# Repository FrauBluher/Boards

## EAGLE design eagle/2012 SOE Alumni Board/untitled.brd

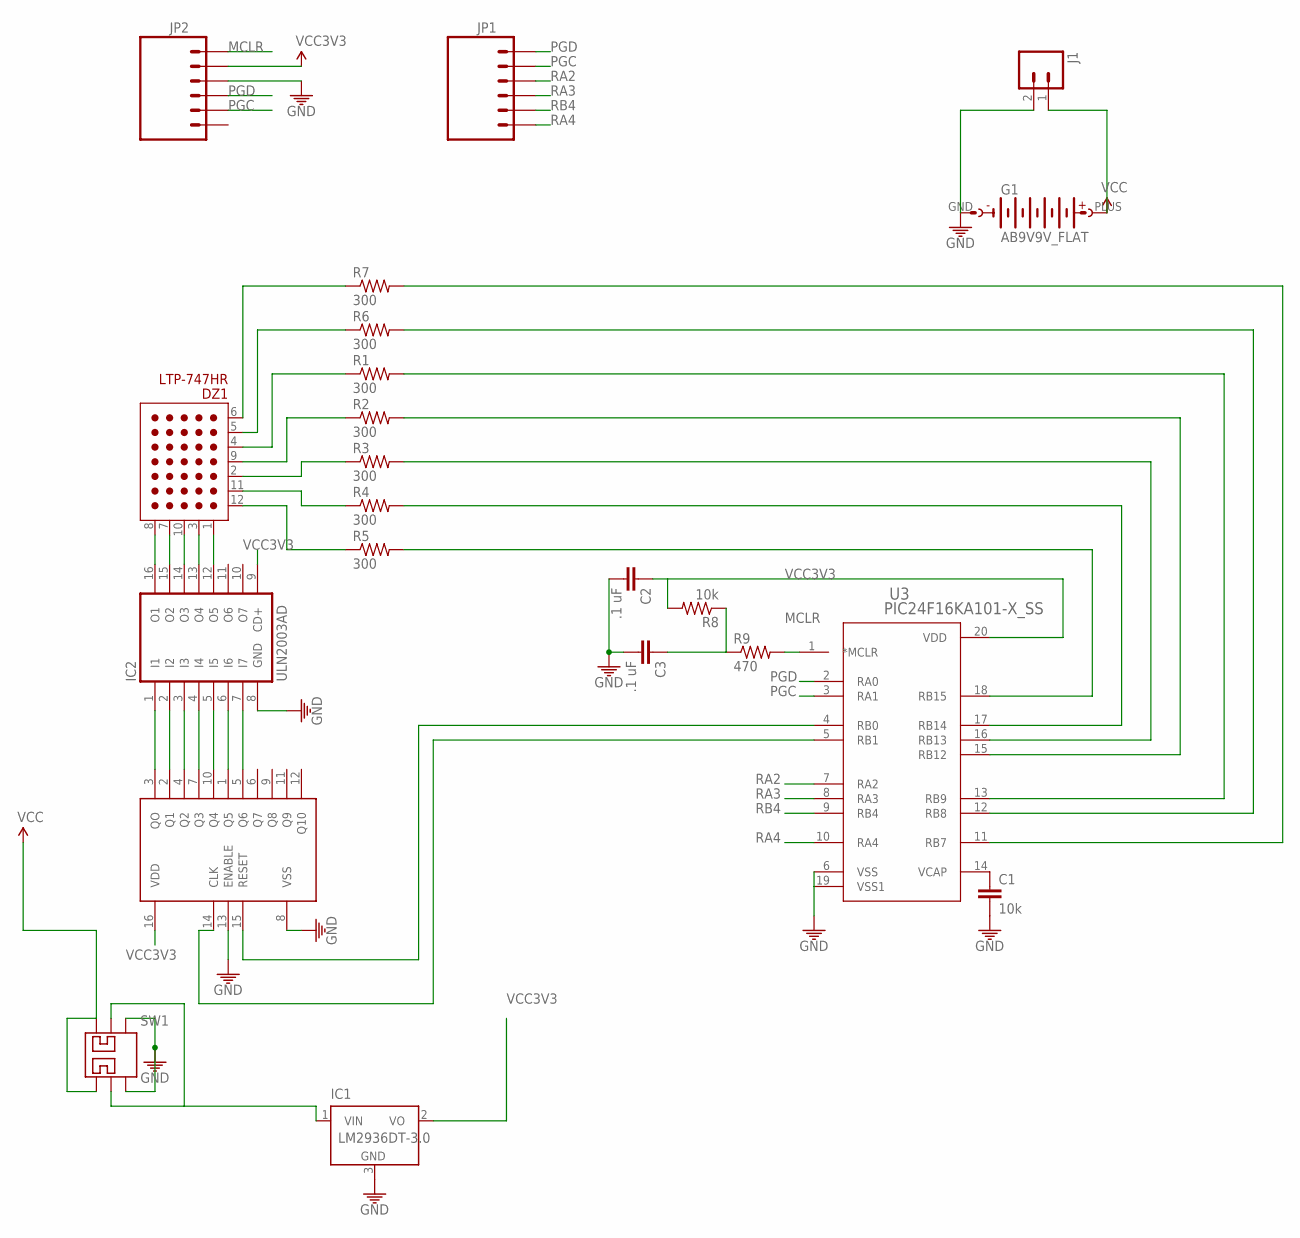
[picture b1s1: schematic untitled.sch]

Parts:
C1: 10k; 1206
C2, C3: .1 uF; 1206
DZ1: LTP-747HR
G1: AB9V9V_FLAT; BH9VPC
IC1: LM2936DT-3.0; TO252
IC2: ULN2003AD; SO16
J1: M02PTH; 1X02
JP1, JP2: M06LOCK; 1X06_LOCK
R1, R2, R3, R4, R5, R6, R7: 300; 0805
R8: 10k; 0805
R9: 470; 0805
SW1: SLIDE_SWITCH_DPDTTOP; EG2207
U1: MC14017B; SO16
U3: PIC24F16KA101-X_SS; SSOP20_MC

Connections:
GND: C1.2, C2.2, C3.2, G1.GND (-), IC1.3 (GND), IC2.8 (GND), J1.2 (1), JP2.3, SW1.P$3, SW1.P$6, U1.8 (VSS), U1.13 (ENABLE), U3.6 (VSS), U3.19 (VSS1)
MCLR: JP2.1, R9.2, U3.1 (*MCLR)
unnamed: DZ1.8 (C5), IC2.16 (O1)
unnamed: DZ1.7 (C4), IC2.15 (O2)
unnamed: DZ1.10 (C3), IC2.14 (O3)
unnamed: DZ1.3 (C2), IC2.13 (O4)
unnamed: DZ1.1 (C1), IC2.12 (O5)
unnamed: IC2.1 (I1), U1.3 (QO)
unnamed: IC2.2 (I2), U1.2 (Q1)
unnamed: IC2.3 (I3), U1.4 (Q2)
unnamed: IC2.4 (I4), U1.7 (Q3)
unnamed: IC2.5 (I5), U1.10 (Q4)
unnamed: IC2.6 (I6), U1.1 (Q5)
unnamed: IC2.7 (I7), U1.5 (Q6)
unnamed: U1.15 (RESET), U3.4 (RB0)
unnamed: U1.14 (CLK), U3.5 (RB1)
unnamed: DZ1.6 (R7), R7.1
unnamed: C1.1, U3.14 (VCAP)
unnamed: DZ1.5 (R6), R6.1
unnamed: DZ1.4 (R5), R1.1
unnamed: DZ1.9 (R4), R2.1
unnamed: DZ1.2 (R3), R3.1
unnamed: DZ1.11 (R2), R4.1
unnamed: DZ1.12 (R1), R5.1
unnamed: IC1.1 (VIN), SW1.P$2, SW1.P$5
unnamed: R5.2, U3.18 (RB15)
unnamed: R4.2, U3.17 (RB14)
unnamed: R3.2, U3.16 (RB13)
unnamed: R2.2, U3.15 (RB12)
unnamed: R1.2, U3.13 (RB9)
unnamed: R6.2, U3.12 (RB8)
unnamed: R7.2, U3.11 (RB7)
unnamed: C3.1, R8.1, R9.1
PGC: JP1.2, JP2.5, U3.3 (RA1)
PGD: JP1.1, JP2.4, U3.2 (RA0)
RA2: JP1.3, U3.7 (RA2)
RA3: JP1.4, U3.8 (RA3)
RA4: JP1.6, U3.10 (RA4)
RB4: JP1.5, U3.9 (RB4)
VCC: G1.PLUS (+), J1.1 (2), SW1.P$1, SW1.P$4
VCC3V3: C2.1, IC1.2 (VO), IC2.9 (CD+), JP2.2, R8.2, U1.16 (VDD), U3.20 (VDD)

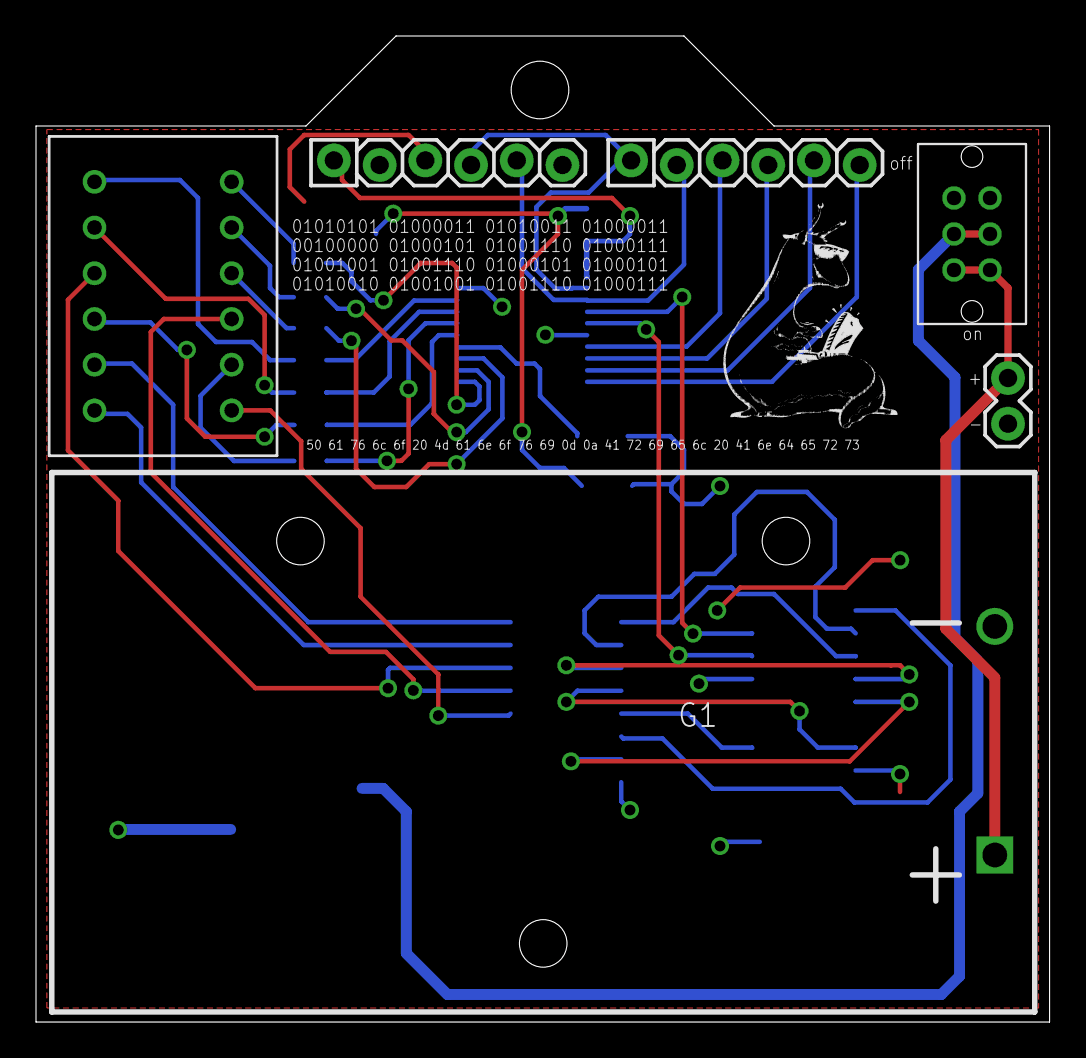
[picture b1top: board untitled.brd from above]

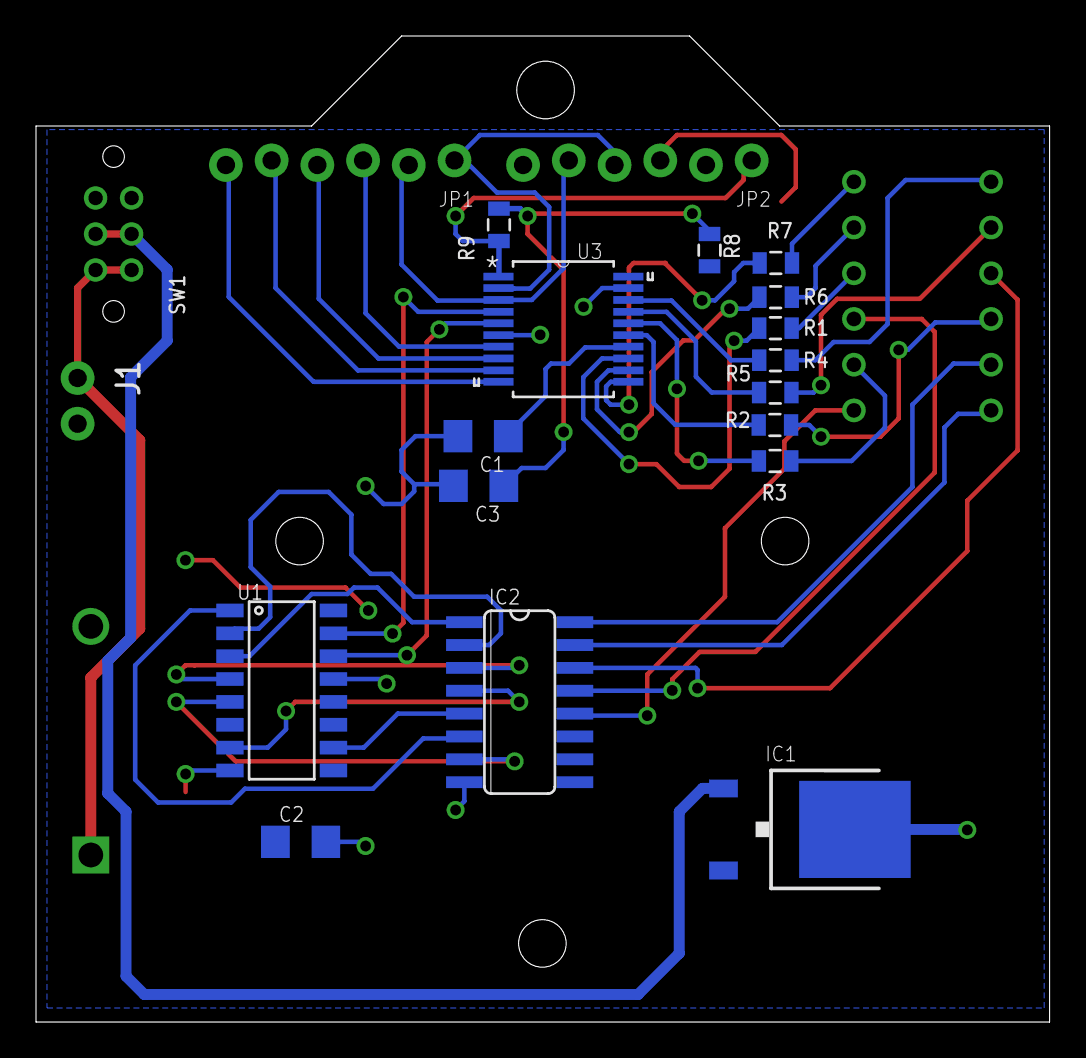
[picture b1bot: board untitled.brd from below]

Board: 2 copper layers, 56.3 x 54.8 mm, 22 parts (16 on the bottom side), 41 nets.

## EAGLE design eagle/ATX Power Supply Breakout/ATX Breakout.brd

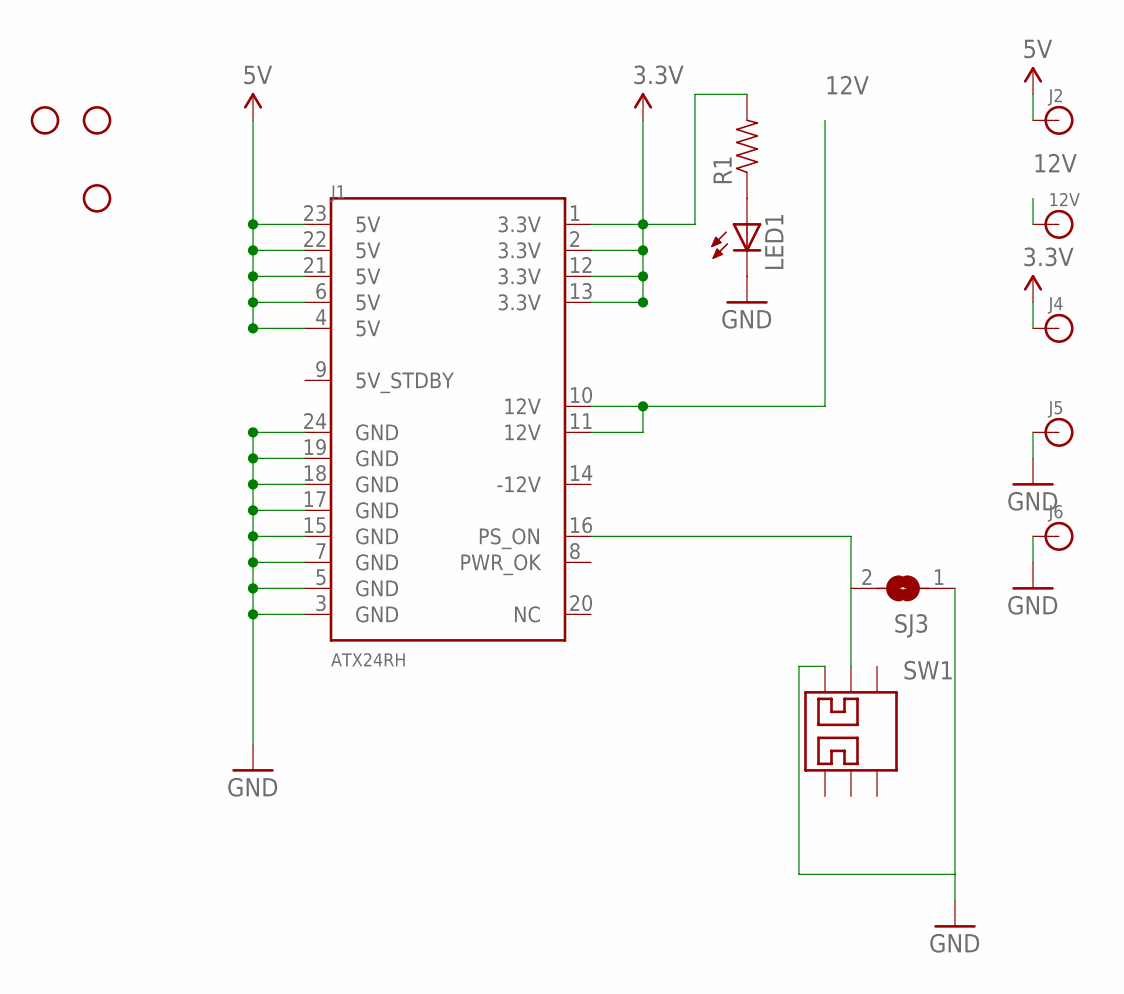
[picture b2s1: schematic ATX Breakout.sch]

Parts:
12V: BANANA_CONN
J1: ATX24RH; ATX24_RIGHT_ANGLE
J2, J4, J5, J6: BANANA_CONN
JP1, JP2, JP3: STAND-OFF
LED1: LED0805; LED-0805
R1: RESISTOR0805-RES; 0805
SJ3: SJ
SW1: SLIDE_SWITCH_DPDTRA; EG2219

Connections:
3.3V: J1.1 (3.3V), J1.2 (3.3V), J1.12 (3.3V), J1.13 (3.3V), J4.P$1, R1.2
5V: J1.4 (5V), J1.6 (5V), J1.21 (5V), J1.22 (5V), J1.23 (5V), J2.P$1
12V: 12V.P$1, J1.10 (12V), J1.11 (12V)
GND: J1.3 (GND), J1.5 (GND), J1.7 (GND), J1.15 (GND), J1.17 (GND), J1.18 (GND), J1.19 (GND), J1.24 (GND), J5.P$1, J6.P$1, LED1.2 (C), SJ3.1, SW1.P$1
unnamed: LED1.1 (A), R1.1
unnamed: J1.16 (PS_ON), SJ3.2, SW1.P$2

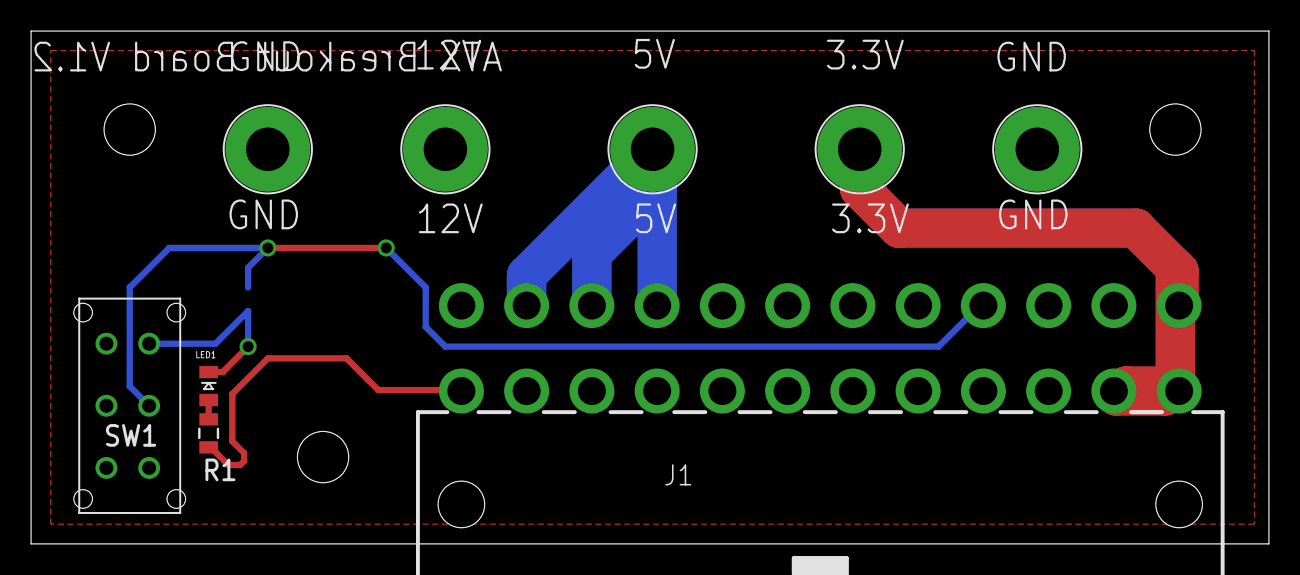
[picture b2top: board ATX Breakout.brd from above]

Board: 2 copper layers, 79.7 x 33.0 mm, 13 parts (1 on the bottom side), 6 nets.

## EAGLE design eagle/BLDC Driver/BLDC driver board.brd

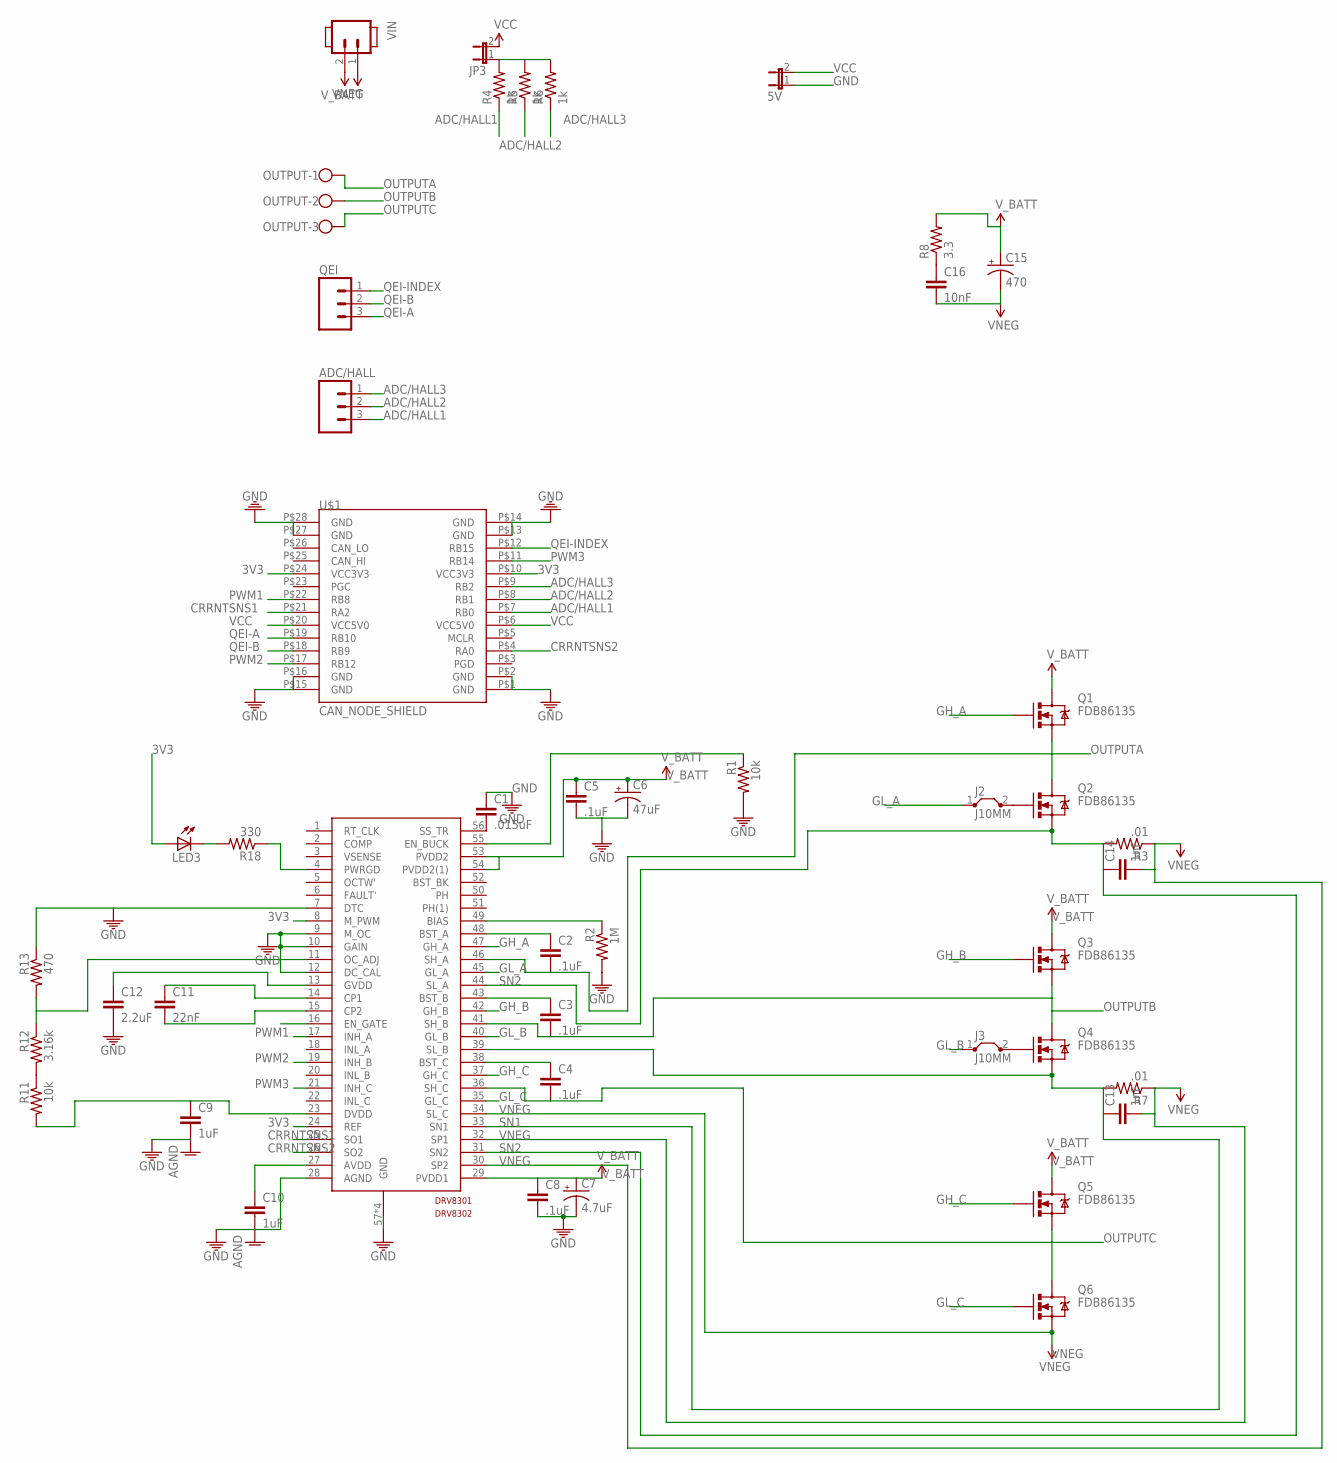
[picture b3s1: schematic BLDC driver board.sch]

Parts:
5V: JP1E; JP1
ADC/HALL: M03LOCK_NO_SILK; 1X03_LOCK_NO_SILK
C1: .015uF; 1206
C2, C3, C4, C5, C8: .1uF; 1206
C6: 47uF; PANASONIC_E
C7: 4.7uF; PANASONIC_E
C9, C10: 1uF; 1206
C11: 22nF; 1206
C12: 2.2uF; 1206
C13, C14: 1nF; 1206
C15: 470; CPOL-RADIAL-1000UF-63V
C16: 10nF; 1206
DRV8301: DRV8302; HTSSOP56
J2, J3: J10MM; 10
JP3: JP1E; JP1
LED3: LED1206; LED-1206
OUTPUT: W237-103
Q1, Q2, Q3, Q4, Q5, Q6: FDB86135; D2PACK
QEI: M03LOCK_NO_SILK; 1X03_LOCK_NO_SILK
R1, R11: 10k; 0805
R2: 1M; 0805
R3, R7: .01; SMT-REF
R4, R5, R6: 1k; 1206
R8: 3.3; 1206
R12: 3.16k; 0805
R13: 470; 0805
R18: 330; 0805
U$1: CAN_NODE_SHIELD
VIN: SCREWTERM02; SCREW_TERMINAL-5.08MM-2

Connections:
3V3: DRV8301.8 (M_PWM), DRV8301.16 (EN_GATE), DRV8301.24 (REF), LED3.A, U$1.P$10 (VCC3V3), U$1.P$24 (VCC3V3)
ADC/HALL1: ADC/HALL.3, R6.1, U$1.P$7 (RB0)
ADC/HALL2: ADC/HALL.2, R5.1, U$1.P$8 (RB1)
ADC/HALL3: ADC/HALL.1, R4.1, U$1.P$9 (RB2)
CRRNTSNS1: DRV8301.25 (SO1), U$1.P$21 (RA2)
CRRNTSNS2: DRV8301.26 (SO2), U$1.P$4 (RA0)
GH_A: DRV8301.47 (GH_A), Q1.1 (G)
GH_B: DRV8301.42 (GH_B), Q3.1 (G)
GH_C: DRV8301.37 (GH_C), Q5.1 (G)
GL_A: DRV8301.45 (GL_A), J2.1
GL_B: DRV8301.40 (GL_B), J3.1
GL_C: DRV8301.35 (GL_C), Q6.1 (G)
GND: 5V.1, C1.1, C5.2, C6.-, C7.-, C8.2, C9.2, C10.2, C12.2, DRV8301.7 (DTC), DRV8301.9 (M_OC), DRV8301.10 (GAIN), DRV8301.12 (DC_CAL), DRV8301.28 (AGND), DRV8301.57 (GND), DRV8301.P$1 (GND), DRV8301.P$2 (GND), DRV8301.P$3 (GND), R1.2, R2.2, R13.1, U$1.P$1 (GND), U$1.P$2 (GND), U$1.P$13 (GND), U$1.P$14 (GND), U$1.P$15 (GND), U$1.P$16 (GND), U$1.P$27 (GND), U$1.P$28 (GND)
unnamed: C1.2, DRV8301.56 (SS_TR)
unnamed: J2.2, Q2.1 (G)
unnamed: DRV8301.49 (BIAS), R2.1
unnamed: C2.1, DRV8301.48 (BST_A)
unnamed: J3.2, Q4.1 (G)
unnamed: C3.1, DRV8301.43 (BST_B)
unnamed: C16.1, R8.1
unnamed: C4.1, DRV8301.38 (BST_C)
unnamed: R11.1, R12.2
unnamed: DRV8301.55 (EN_BUCK), R1.1
unnamed: DRV8301.4 (PWRGD), R18.1
unnamed: DRV8301.11 (OC_ADJ), R12.1, R13.2
unnamed: JP3.1, R4.2, R5.2, R6.2
unnamed: LED3.C, R18.2
unnamed: C10.1, DRV8301.27 (AVDD)
unnamed: C9.1, DRV8301.23 (DVDD), R11.2
unnamed: C11.1, DRV8301.14 (CP1)
unnamed: C11.2, DRV8301.15 (CP2)
unnamed: C12.1, DRV8301.13 (GVDD)
OUTPUTA: C2.2, DRV8301.46 (SH_A), OUTPUT.1, Q1.3 (S), Q2.2 (D), Q2.P$1 (D), Q2.P$2 (D), Q2.P$3 (D), Q2.P$4 (D), Q2.P$5 (D), Q2.P$6 (D), Q2.P$7 (D), Q2.P$8 (D), Q2.P$9 (D), Q2.P$10 (D), Q2.P$11 (D), Q2.P$12 (D)
OUTPUTB: C3.2, DRV8301.41 (SH_B), OUTPUT.2, Q3.3 (S), Q4.2 (D), Q4.P$1 (D), Q4.P$2 (D), Q4.P$3 (D), Q4.P$4 (D), Q4.P$5 (D), Q4.P$6 (D), Q4.P$7 (D), Q4.P$8 (D), Q4.P$9 (D), Q4.P$10 (D), Q4.P$11 (D), Q4.P$12 (D)
OUTPUTC: C4.2, DRV8301.36 (SH_C), OUTPUT.3, Q5.3 (S), Q6.2 (D), Q6.P$1 (D), Q6.P$2 (D), Q6.P$3 (D), Q6.P$4 (D), Q6.P$5 (D), Q6.P$6 (D), Q6.P$7 (D), Q6.P$8 (D), Q6.P$9 (D), Q6.P$10 (D), Q6.P$11 (D), Q6.P$12 (D)
PWM1: DRV8301.17 (INH_A), U$1.P$22 (RB8)
PWM2: DRV8301.19 (INH_B), U$1.P$17 (RB12)
PWM3: DRV8301.21 (INH_C), U$1.P$11 (RB14)
QEI-A: QEI.3, U$1.P$19 (RB10)
QEI-B: QEI.2, U$1.P$18 (RB9)
QEI-INDEX: QEI.1, U$1.P$12 (RB15)
SN1: C13.1, DRV8301.33 (SN1), DRV8301.39 (SL_B), Q4.3 (S), R7.2
SN2: C14.1, DRV8301.31 (SN2), DRV8301.44 (SL_A), Q2.3 (S), R3.2
VCC: 5V.2, JP3.2, U$1.P$6 (VCC5V0), U$1.P$20 (VCC5V0)
VNEG: C13.2, C14.2, C15.2 (-), C16.2, DRV8301.30 (SP2), DRV8301.32 (SP1), DRV8301.34 (SL_C), Q6.3 (S), R3.1, R7.1, VIN.2
V_BATT: C5.1, C6.+, C7.+, C8.1, C15.1 (+), DRV8301.29 (PVDD1), DRV8301.53 (PVDD2), DRV8301.54 (PVDD2(1)), Q1.2 (D), Q1.P$1 (D), Q1.P$2 (D), Q1.P$3 (D), Q1.P$4 (D), Q1.P$5 (D), Q1.P$6 (D), Q1.P$7 (D), Q1.P$8 (D), Q1.P$9 (D), Q1.P$10 (D), Q1.P$11 (D), Q1.P$12 (D), Q3.2 (D), Q3.P$1 (D), Q3.P$2 (D), Q3.P$3 (D), Q3.P$4 (D), Q3.P$5 (D), Q3.P$6 (D), Q3.P$7 (D), Q3.P$8 (D), Q3.P$9 (D), Q3.P$10 (D), Q3.P$11 (D), Q3.P$12 (D), Q5.2 (D), Q5.P$1 (D), Q5.P$2 (D), Q5.P$3 (D), Q5.P$4 (D), Q5.P$5 (D), Q5.P$6 (D), Q5.P$7 (D), Q5.P$8 (D), Q5.P$9 (D), Q5.P$10 (D), Q5.P$11 (D), Q5.P$12 (D), R8.2, VIN.1

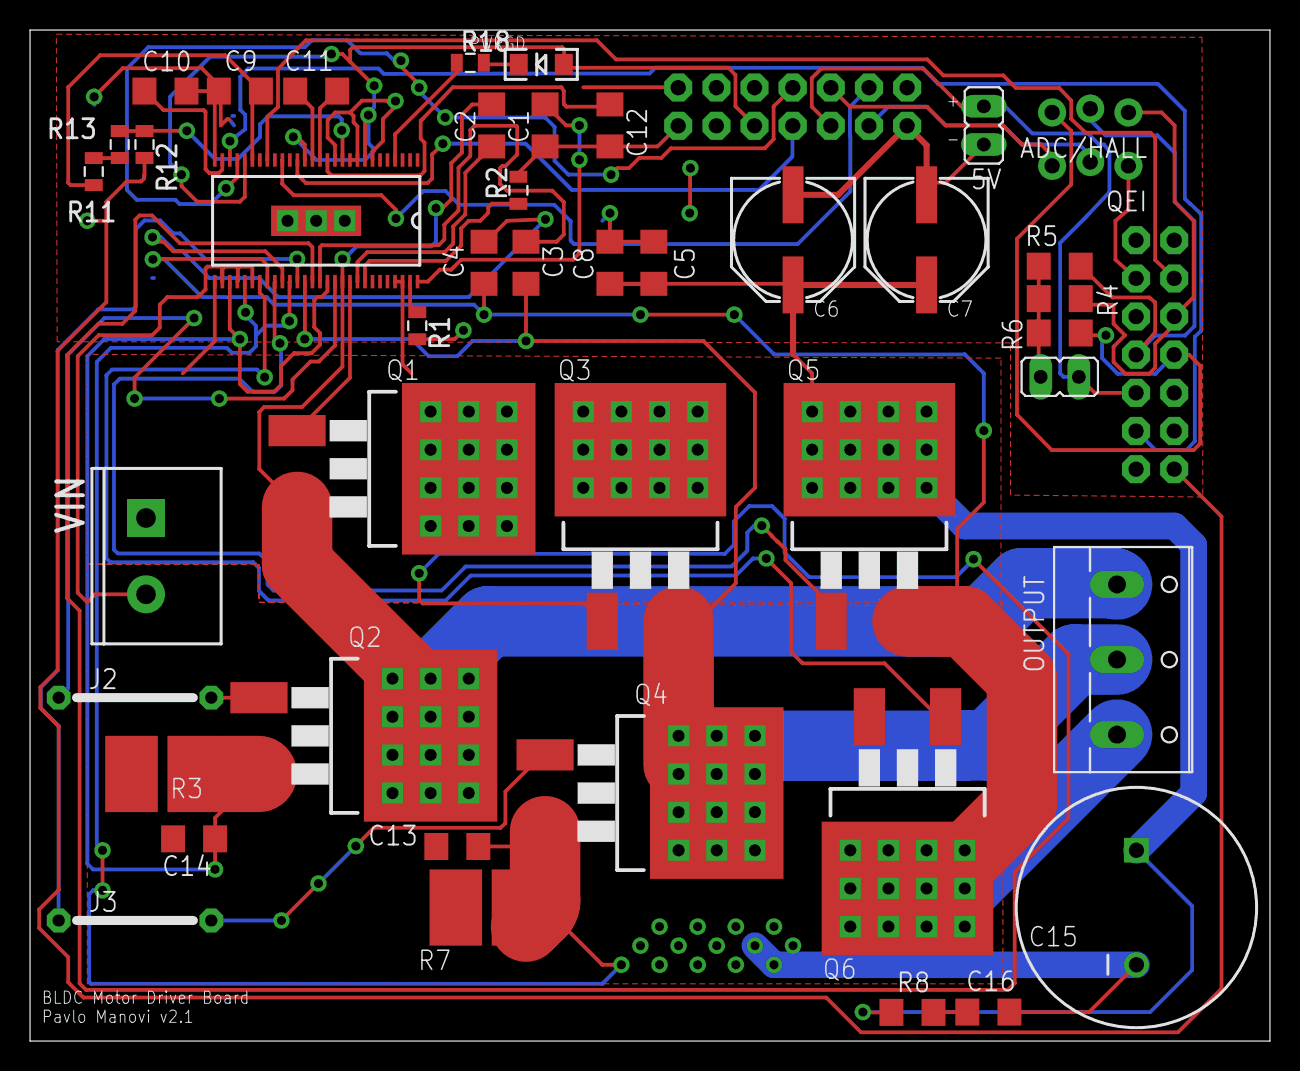
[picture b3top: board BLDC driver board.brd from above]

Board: 2 copper layers, 82.5 x 67.3 mm, 45 parts (0 on the bottom side), 46 nets.

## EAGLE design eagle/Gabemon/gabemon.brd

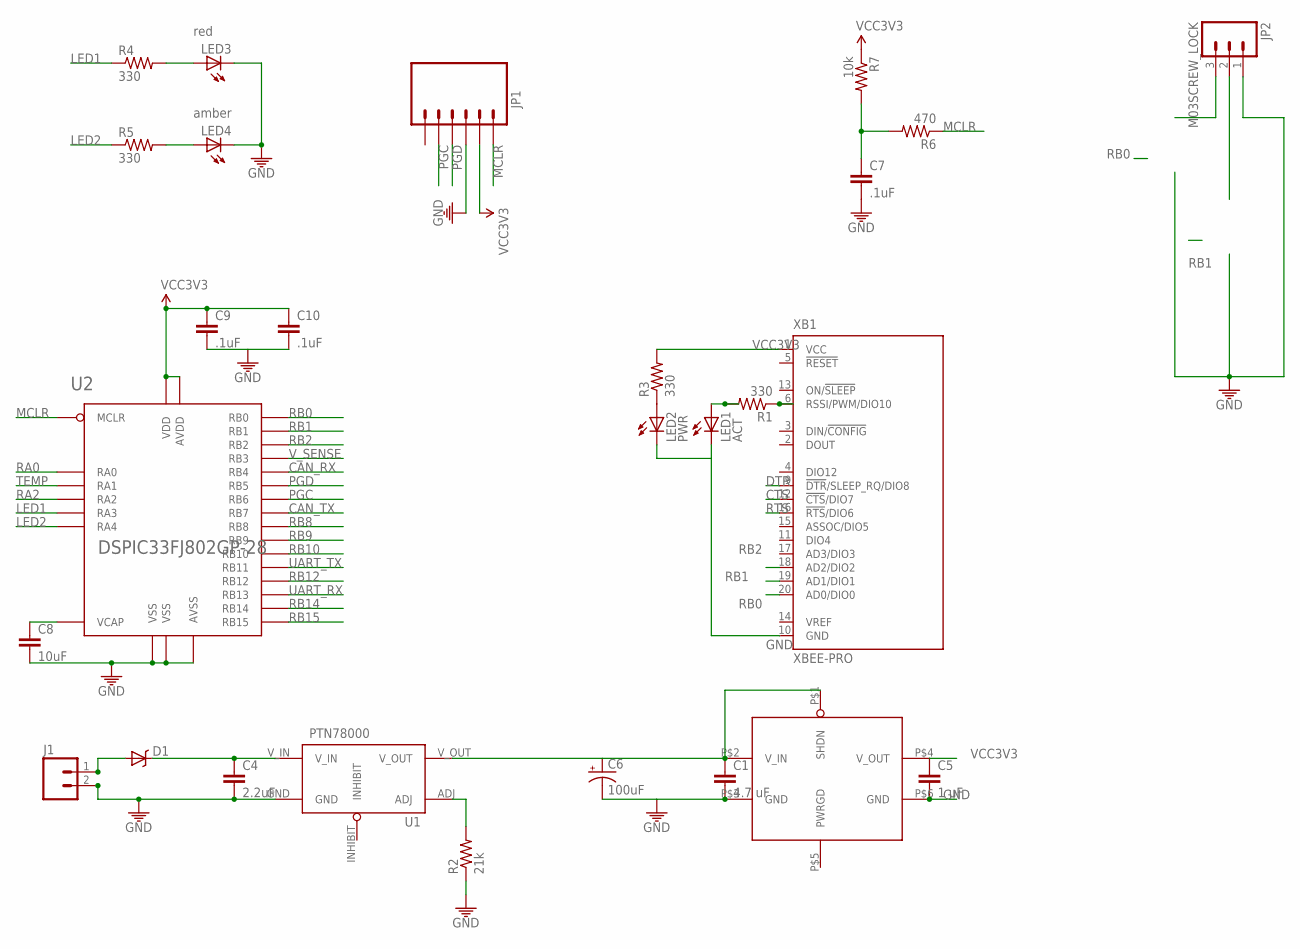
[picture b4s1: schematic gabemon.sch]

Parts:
C1: 4.7 uF; 1206
C4: 2.2uF; 1206
C5: 1 uF; 1206
C6: 100uF; CPOL_6.6
C7, C9, C10: .1uF; 1206
C8: 10uF; 1206
D1: DIODE-SCHOTTKY240A; SMA-DIODE-B240A
J1: M023.5MM-NO_SILK; SCREWTERMINAL-3.5MM-2-NS
JP1: M06LOCK; 1X06_LOCK
JP2: M03SCREW_LOCK; SCREWTERMINAL-3.5MM-3_LOCK.007S
LED1: ACT; LED-1206
LED2: PWR; LED-1206
LED3, LED4: LED1206; LED-1206
R1, R3, R4, R5: 330; 0805
R2: 21k; 0805
R6: 470; 0805
R7: 10k; 0805
U1: PTN78000
U2: DSPIC33FJ802GP-28; SOIC28-W
U$2: MCP1826; SOT223-5
XB1: XBEE-PRO

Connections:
CAN_RX: U2.P$11 (RB4)
CAN_TX: U2.P$16 (RB7)
CTS: XB1.12 (!CTS!/DIO7)
DTR: XB1.9 (!DTR!/SLEEP_RQ/DIO8)
GND: C1.2, C4.2, C5.2, C6.-, C7.2, C8.2, C9.2, C10.2, J1.2 (1), JP1.3, JP2.1, LED1.C, LED2.C, LED3.C, LED4.C, R2.1, U1.GND, U2.P$8 (VSS), U2.P$19 (VSS), U2.P$27 (AVSS), U$2.P$3 (GND), U$2.P$6 (GND), XB1.10 (GND)
LED1: R4.1, U2.P$10 (RA3)
LED2: R5.1, U2.P$12 (RA4)
MCLR: JP1.1, R6.1, U2.P$1 (MCLR)
unnamed: LED3.A, R4.2
unnamed: R1.1, XB1.6 (RSSI/PWM/DIO10)
unnamed: LED4.A, R5.2
unnamed: LED1.A, R1.2
unnamed: LED2.A, R3.1
unnamed: R2.2, U1.ADJ
unnamed: C7.1, R6.2, R7.2
unnamed: C4.1, D1.C, U1.V_IN
unnamed: D1.A, J1.1 (2)
unnamed: C8.1, U2.P$20 (VCAP)
PGC: JP1.5, U2.P$15 (RB6)
PGD: JP1.4, U2.P$14 (RB5)
RA0: U2.P$2 (RA0)
RA2: U2.P$9 (RA2)
RB0: U2.P$4 (RB0), XB1.20 (AD0/DIO0)
RB1: U2.P$5 (RB1), XB1.19 (AD1/DIO1)
RB2: U2.P$6 (RB2), XB1.18 (AD2/DIO2)
RB8: U2.P$17 (RB8)
RB9: U2.P$18 (RB9)
RB10: U2.P$22 (RB10)
RB12: U2.P$23 (RB12)
RB14: U2.P$25 (RB14)
RB15: U2.P$26 (RB15)
RTS: XB1.16 (!RTS!/DIO6)
TEMP: U2.P$3 (RA1)
UART_RX: U2.P$24 (RB13)
UART_TX: U2.P$21 (RB11)
VCC: C1.1, C6.+, U1.V_OUT, U$2.P$1 (SHDN), U$2.P$2 (V_IN)
VCC3V3: C5.1, C9.1, C10.1, JP1.2, R3.2, R7.1, U2.P$13 (VDD), U2.P$28 (AVDD), U$2.P$4 (V_OUT), XB1.1 (VCC)
V_SENSE: U2.P$7 (RB3)

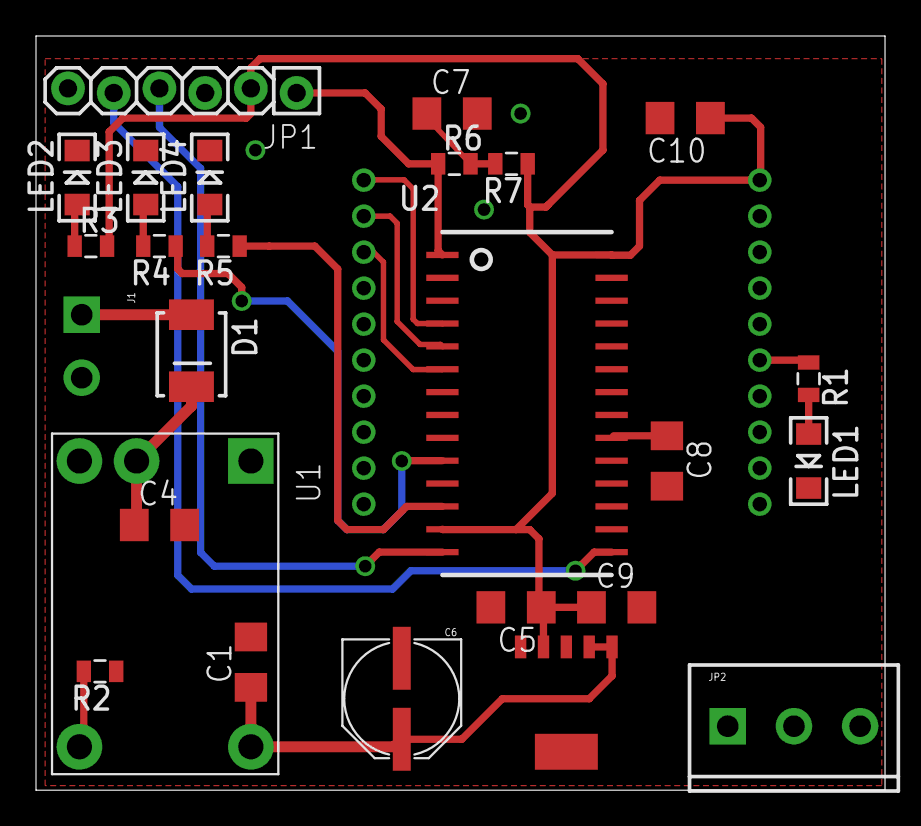
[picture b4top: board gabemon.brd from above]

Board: 2 copper layers, 47.2 x 41.9 mm, 27 parts (1 on the bottom side), 21 nets.

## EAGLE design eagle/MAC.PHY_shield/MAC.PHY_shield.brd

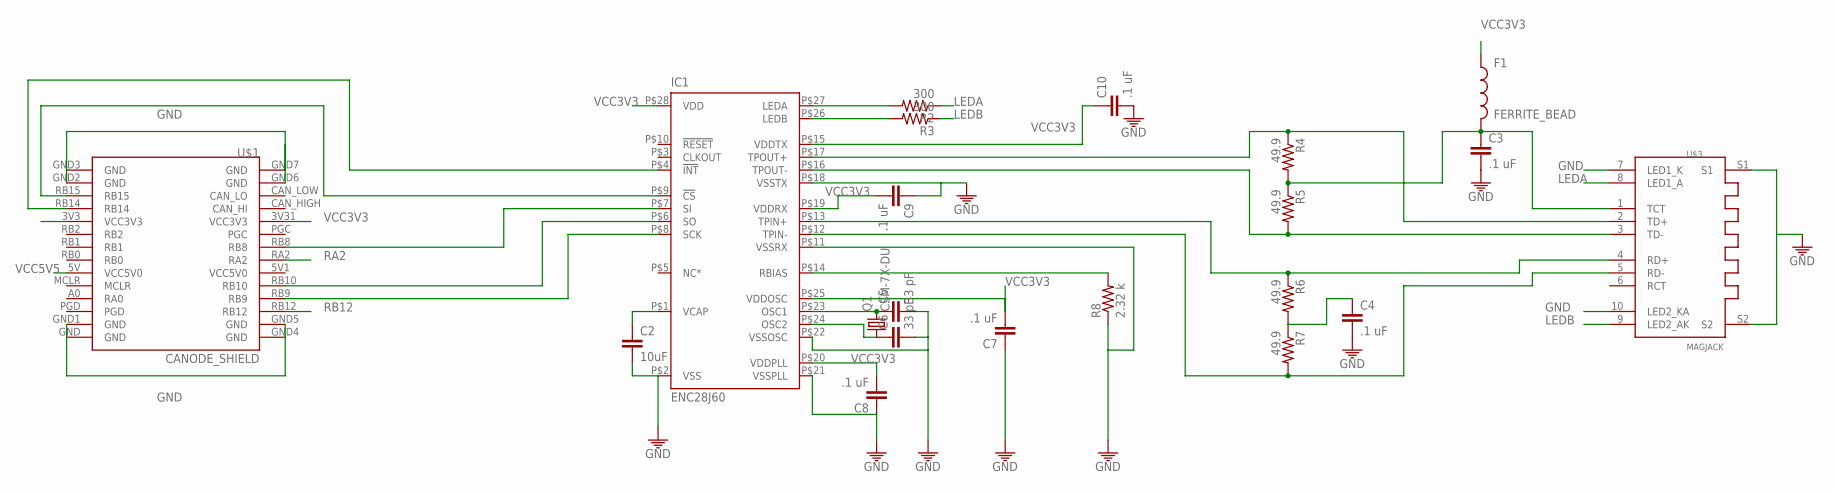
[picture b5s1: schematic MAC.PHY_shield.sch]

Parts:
C2: 10uF; 1206
C3, C4, C7, C8, C9, C10: .1 uF; 1206
C5, C6: 33 pF; 1206
F1: FERRITE_BEAD; 1206
IC1: ENC28J60; SOIC28-W
Q1: CSM-7X-DU
R2, R3: 300; 0805
R4, R5, R6, R7: 49.9; 0805
R8: 2.32 k; 0805
U$1: CANODE_SHIELD
U$3: MAGJACK; 08B0-1X1T-06-F

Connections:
GND: C2.2, C3.2, C4.2, C5.2, C6.2, C7.1, C8.1, C9.1, C10.2, IC1.P$2 (VSS), IC1.P$11 (VSSRX), IC1.P$18 (VSSTX), IC1.P$21 (VSSPLL), IC1.P$22 (VSSOSC), R8.1, U$1.GND, U$1.GND1 (GND), U$1.GND2 (GND), U$1.GND3 (GND), U$1.GND4 (GND), U$1.GND5 (GND), U$1.GND6 (GND), U$1.GND7 (GND), U$3.7 (LED1_K), U$3.10 (LED2_KA), U$3.S1, U$3.S2
LEDA: R2.1, U$3.8 (LED1_A)
LEDB: R3.1, U$3.9 (LED2_AK)
unnamed: C2.1, IC1.P$1 (VCAP)
unnamed: IC1.P$27 (LEDA), R2.2
unnamed: IC1.P$26 (LEDB), R3.2
unnamed: C3.1, F1.2, R4.2, R5.1, U$3.1 (TCT)
unnamed: IC1.P$17 (TPOUT+), R4.1, U$3.2 (TD+)
unnamed: IC1.P$16 (TPOUT-), R5.2, U$3.3 (TD-)
unnamed: IC1.P$13 (TPIN+), R6.1, U$3.4 (RD+)
unnamed: C4.1, R6.2, R7.1
unnamed: IC1.P$12 (TPIN-), R7.2, U$3.5 (RD-)
unnamed: IC1.P$9 (!CS), U$1.RB15
unnamed: IC1.P$14 (RBIAS), R8.2
unnamed: IC1.P$8 (SCK), U$1.RB9
unnamed: C5.1, IC1.P$23 (OSC1), Q1.2
unnamed: C6.1, IC1.P$24 (OSC2), Q1.1
unnamed: IC1.P$6 (SO), U$1.RB10
unnamed: IC1.P$7 (SI), U$1.RB8
unnamed: IC1.P$4 (!INT), U$1.RB14
RA2: U$1.RA2
RB12: U$1.RB12
VCC3V3: C7.2, C8.2, C9.2, C10.1, F1.1, IC1.P$15 (VDDTX), IC1.P$19 (VDDRX), IC1.P$20 (VDDPLL), IC1.P$25 (VDDOSC), IC1.P$28 (VDD), U$1.3V3 (VCC3V3), U$1.3V31 (VCC3V3)
VCC5V5: U$1.5V (VCC5V0)

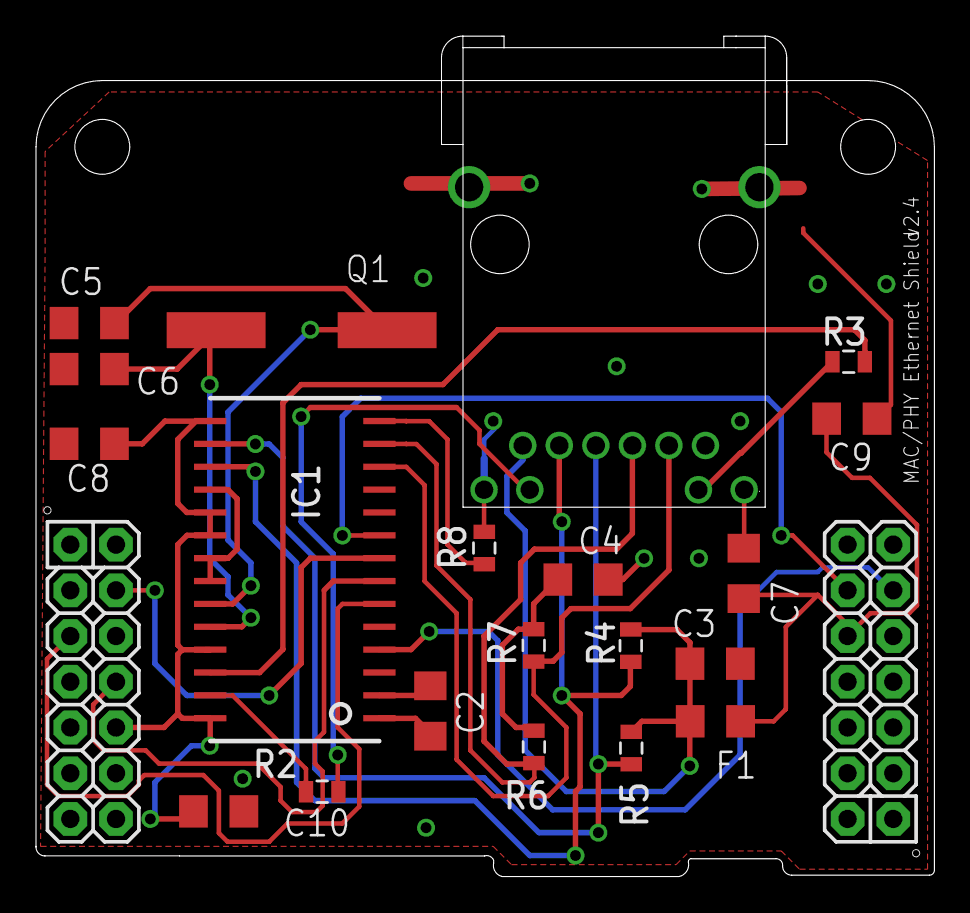
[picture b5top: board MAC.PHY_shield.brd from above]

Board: 2 copper layers, 49.9 x 46.7 mm, 23 parts (0 on the bottom side), 21 nets.

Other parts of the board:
E$3, E$4: STAND-OFF-TIGHT

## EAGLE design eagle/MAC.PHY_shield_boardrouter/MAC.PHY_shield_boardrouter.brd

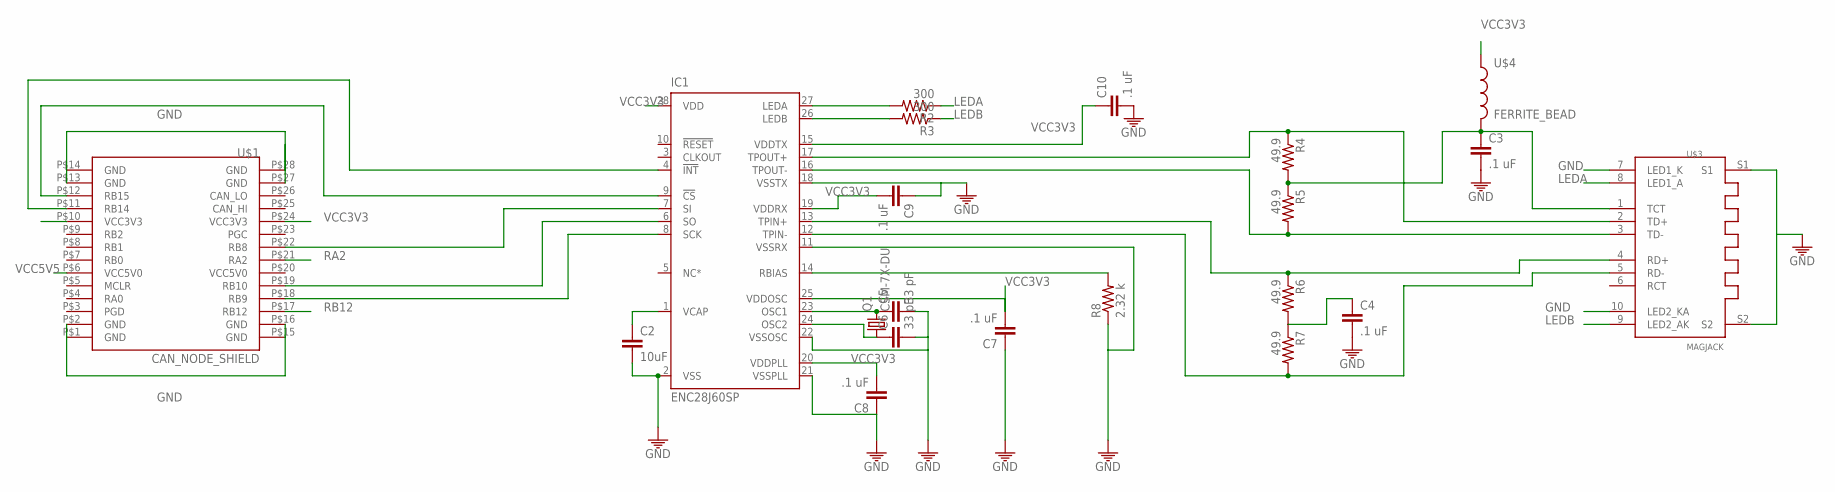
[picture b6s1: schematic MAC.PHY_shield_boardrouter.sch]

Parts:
C2: 10uF; 1206
C3, C4, C7, C8, C9, C10: .1 uF; 1206
C5, C6: 33 pF; 1206
IC1: ENC28J60SP; DIL28-3
Q1: CSM-7X-DU
R2, R3: 300; 0805
R4, R5, R6, R7: 49.9; 0805
R8: 2.32 k; 0805
U$1: CAN_NODE_SHIELD
U$3: MAGJACK; 08B0-1X1T-06-F
U$4: FERRITE_BEAD; 1206

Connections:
GND: C2.2, C3.2, C4.2, C5.2, C6.2, C7.1, C8.1, C9.1, C10.2, IC1.2 (VSS), IC1.11 (VSSRX), IC1.18 (VSSTX), IC1.21 (VSSPLL), IC1.22 (VSSOSC), R8.1, U$1.P$1 (GND), U$1.P$2 (GND), U$1.P$13 (GND), U$1.P$14 (GND), U$1.P$15 (GND), U$1.P$16 (GND), U$1.P$27 (GND), U$1.P$28 (GND), U$3.7 (LED1_K), U$3.10 (LED2_KA), U$3.S1, U$3.S2
LEDA: R2.1, U$3.8 (LED1_A)
LEDB: R3.1, U$3.9 (LED2_AK)
unnamed: C2.1, IC1.1 (VCAP)
unnamed: IC1.27 (LEDA), R2.2
unnamed: IC1.26 (LEDB), R3.2
unnamed: C3.1, R4.2, R5.1, U$3.1 (TCT), U$4.2
unnamed: IC1.17 (TPOUT+), R4.1, U$3.2 (TD+)
unnamed: IC1.16 (TPOUT-), R5.2, U$3.3 (TD-)
unnamed: IC1.13 (TPIN+), R6.1, U$3.4 (RD+)
unnamed: C4.1, R6.2, R7.1
unnamed: IC1.12 (TPIN-), R7.2, U$3.5 (RD-)
unnamed: IC1.9 (!CS), U$1.P$12 (RB15)
unnamed: IC1.14 (RBIAS), R8.2
unnamed: IC1.8 (SCK), U$1.P$18 (RB9)
unnamed: C5.1, IC1.23 (OSC1), Q1.2
unnamed: C6.1, IC1.24 (OSC2), Q1.1
unnamed: IC1.6 (SO), U$1.P$19 (RB10)
unnamed: IC1.7 (SI), U$1.P$22 (RB8)
unnamed: IC1.4 (!INT), U$1.P$11 (RB14)
RA2: U$1.P$21 (RA2)
RB12: U$1.P$17 (RB12)
VCC3V3: C7.2, C8.2, C9.2, C10.1, IC1.15 (VDDTX), IC1.19 (VDDRX), IC1.20 (VDDPLL), IC1.25 (VDDOSC), IC1.28 (VDD), U$1.P$10 (VCC3V3), U$1.P$24 (VCC3V3), U$4.1
VCC5V5: U$1.P$6 (VCC5V0)

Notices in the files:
parts and their libraries:
SparkFun-Connectors: Licensing: CC v3.0 Share-Alike You are welcome to use this library for commercial purposes.
ublox TIMB: © u-blox ag, 1997-2003
